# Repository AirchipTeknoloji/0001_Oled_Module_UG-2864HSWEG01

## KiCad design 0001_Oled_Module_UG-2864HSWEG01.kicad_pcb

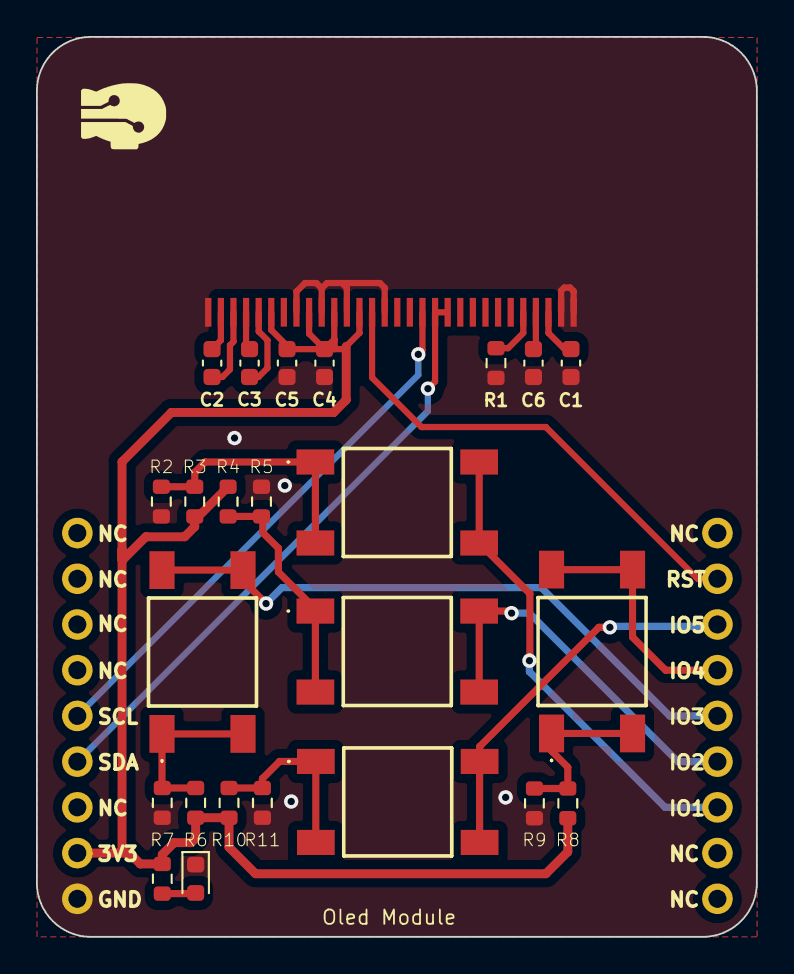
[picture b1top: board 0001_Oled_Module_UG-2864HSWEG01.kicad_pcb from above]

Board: 2 copper layers, 40.0 x 50.0 mm, 26 parts (0 on the bottom side), 23 nets.

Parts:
C1, C4, C5: 10uF; C_0603_1608Metric
C2, C3, C6: 2.2uF; C_0603_1608Metric
D1: LED; LED_0603_1608Metric
R1: 390k; R_0603_1608Metric
R2, R3, R4, R5, R6, R7, R8, R9, R10, R11: 0r; R_0603_1608Metric
R12: 470r; R_0603_1608Metric
SW1, SW2, SW3, SW4, SW5: SW_MEC_5E; TS046665BK160SMT
U1: UG-2864HSWEG01; 1X30-0.7MM
U2: pin_header_5-3

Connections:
+3V3: C4.1, C5.1, R3.1, R4.1, R6.1, R8.1, R10.1, R12.1, U1.6 (VBAT), U1.9 (VDD), U1.11 (BS1), U1.13 (/CS), U2.8
GND: C1.2, C4.2, C5.2, C6.2, D1.1 (K), R1.1, R2.1, R5.1, R7.1, R9.1, R11.1, U1.1 (MT), U1.8 (VSS), U1.10 (BS0), U1.12 (BS2), U1.15 (D/C), U1.29 (VLSS), U1.30 (MT2), U2.9
GPIO_01: SW1.3 (K), SW1.4 (A), U2.12
GPIO_02: SW2.3 (K), SW2.4 (A), U2.13
GPIO_03: SW3.3 (K), SW3.4 (A), U2.14
GPIO_04: SW4.3 (K), SW4.4 (A), U2.15
GPIO_05: SW5.3 (K), SW5.4 (A), U2.16
unnamed: D1.2 (A), R12.2
unnamed: R2.2, R3.2, SW1.1, SW1.2
unnamed: R4.2, R5.2, SW2.1, SW2.2
unnamed: R6.2, R7.2, SW3.1, SW3.2
unnamed: R8.2, R9.2, SW4.1, SW4.2
unnamed: R10.2, R11.2, SW5.1, SW5.2
unnamed: C3.2, U1.5 (C1N)
unnamed: C3.1, U1.4 (C1P)
unnamed: C2.2, U1.3 (C2N)
unnamed: C2.1, U1.2 (C2P)
unnamed: R1.2, U1.26 (IREF)
unnamed: C1.1, U1.28 (VCC)
unnamed: C6.1, U1.27 (VCOMH)
RST: U1.14 (/RES), U2.17
SCL: U1.18 (D0/DI), U2.5
SDA: U1.19 (D1/SCLK), U1.20 (D2), U2.6
